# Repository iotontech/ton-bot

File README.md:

TON-BOT V1.1
========

O robô **TON-BOT** é um kit de robótica móvel 3 em 1 com a **Plataforma TON**, destinado ao aprendizado no desenvolvimento de robôs solucionadores de labirinto (micromouse) e robôs seguidores de linha (robotracer). Também podendo ser controlado sem fio pelo Bluetooth.

# Características do Kit

* Motores: micromotor Pololu com caixa de redução de metal - 1000 rpm
* Rodas: 32x7mm (plástico e borracha)
* Encoders: magnético em quadratura - 360 ppr
* 8 Sensores de linha: QRE1113GR
* 4 Sensores de parede: SFH4545 (LED) / TEFT4300 (fototransistor)
* Ponte H dos motores: TB6612FNG
* Bateria: LiPo 1S 600mAh

Com os recursos do **TON** o kit possui: Carregador integrado + Monitor de bateria + Bluetooth 4.0 + Buzzer + accel/gyro/mag + LED RGB + Wi-Fi

# Primeiros Passos

1. Execute o código de testes do robô:
    * O **TON-BOT** é enviado com o código [ton-bot_teste](https://github.com/iotontech/ton-bot_teste) já gravado!
    * Então, conecte o robô em uma porta USB e abra o terminal (baudrate 115200)
    * São apresentadas as leituras de todos os sensores
    * Para testar os motores basta ligar a chave *MOTORS* e pressionar o botão *USER*
    * **Para recarregar a bateria:** conecte o robô no carregador com o botão *USER* pressionado (pode liberá-lo logo em seguida). Quando o LED estiver verde e piscando indica que a bateria já está carregada
2. Siga os passos deste [link](https://github.com/iotontech/IOTON-IDE) para a instalação da *IOTON-IDE* **OU** siga este [tutorial](https://github.com/iotontech/ioton-mbed-online) para usar o *mbed Online Compiler*
3. Programando seu robô:
    * Faça uma cópia do [código de teste](https://github.com/iotontech/ton-bot_teste) e utilize ele de referência
    * Abra o **Editor Atom** e adicione a pasta do projeto: `File→Add Project Folder...`
    * Edite o arquivo *main.cpp*
4. Procedimentos para gravação do código no robô:
    * Colocar o TON no modo **BOOT**: pressionar o botão *RESET/BOOT* por mais de 1s
    * Realizar o **upload**: clicar no botão *“PlatformIO: Upload”* (icone: seta para direita)
    * Aguardar o término do processo
    * Voltar o TON para a execução: pressione rapidamente o botão *RESET/BOOT*

# License

Copyright IOTON Technology 2017.

This documentation describes Open Hardware and is licensed under the CERN OHL v. 1.2.
You may redistribute and modify this documentation under the terms of the CERN OHL v.1.2. (http://ohwr.org/cernohl). This documentation is distributed WITHOUT ANY EXPRESS OR IMPLIED WARRANTY, INCLUDING OF MERCHANTABILITY, SATISFACTORY QUALITY AND FITNESS FOR A PARTICULAR PURPOSE. Please see the CERN OHL v.1.2 for applicable conditions.

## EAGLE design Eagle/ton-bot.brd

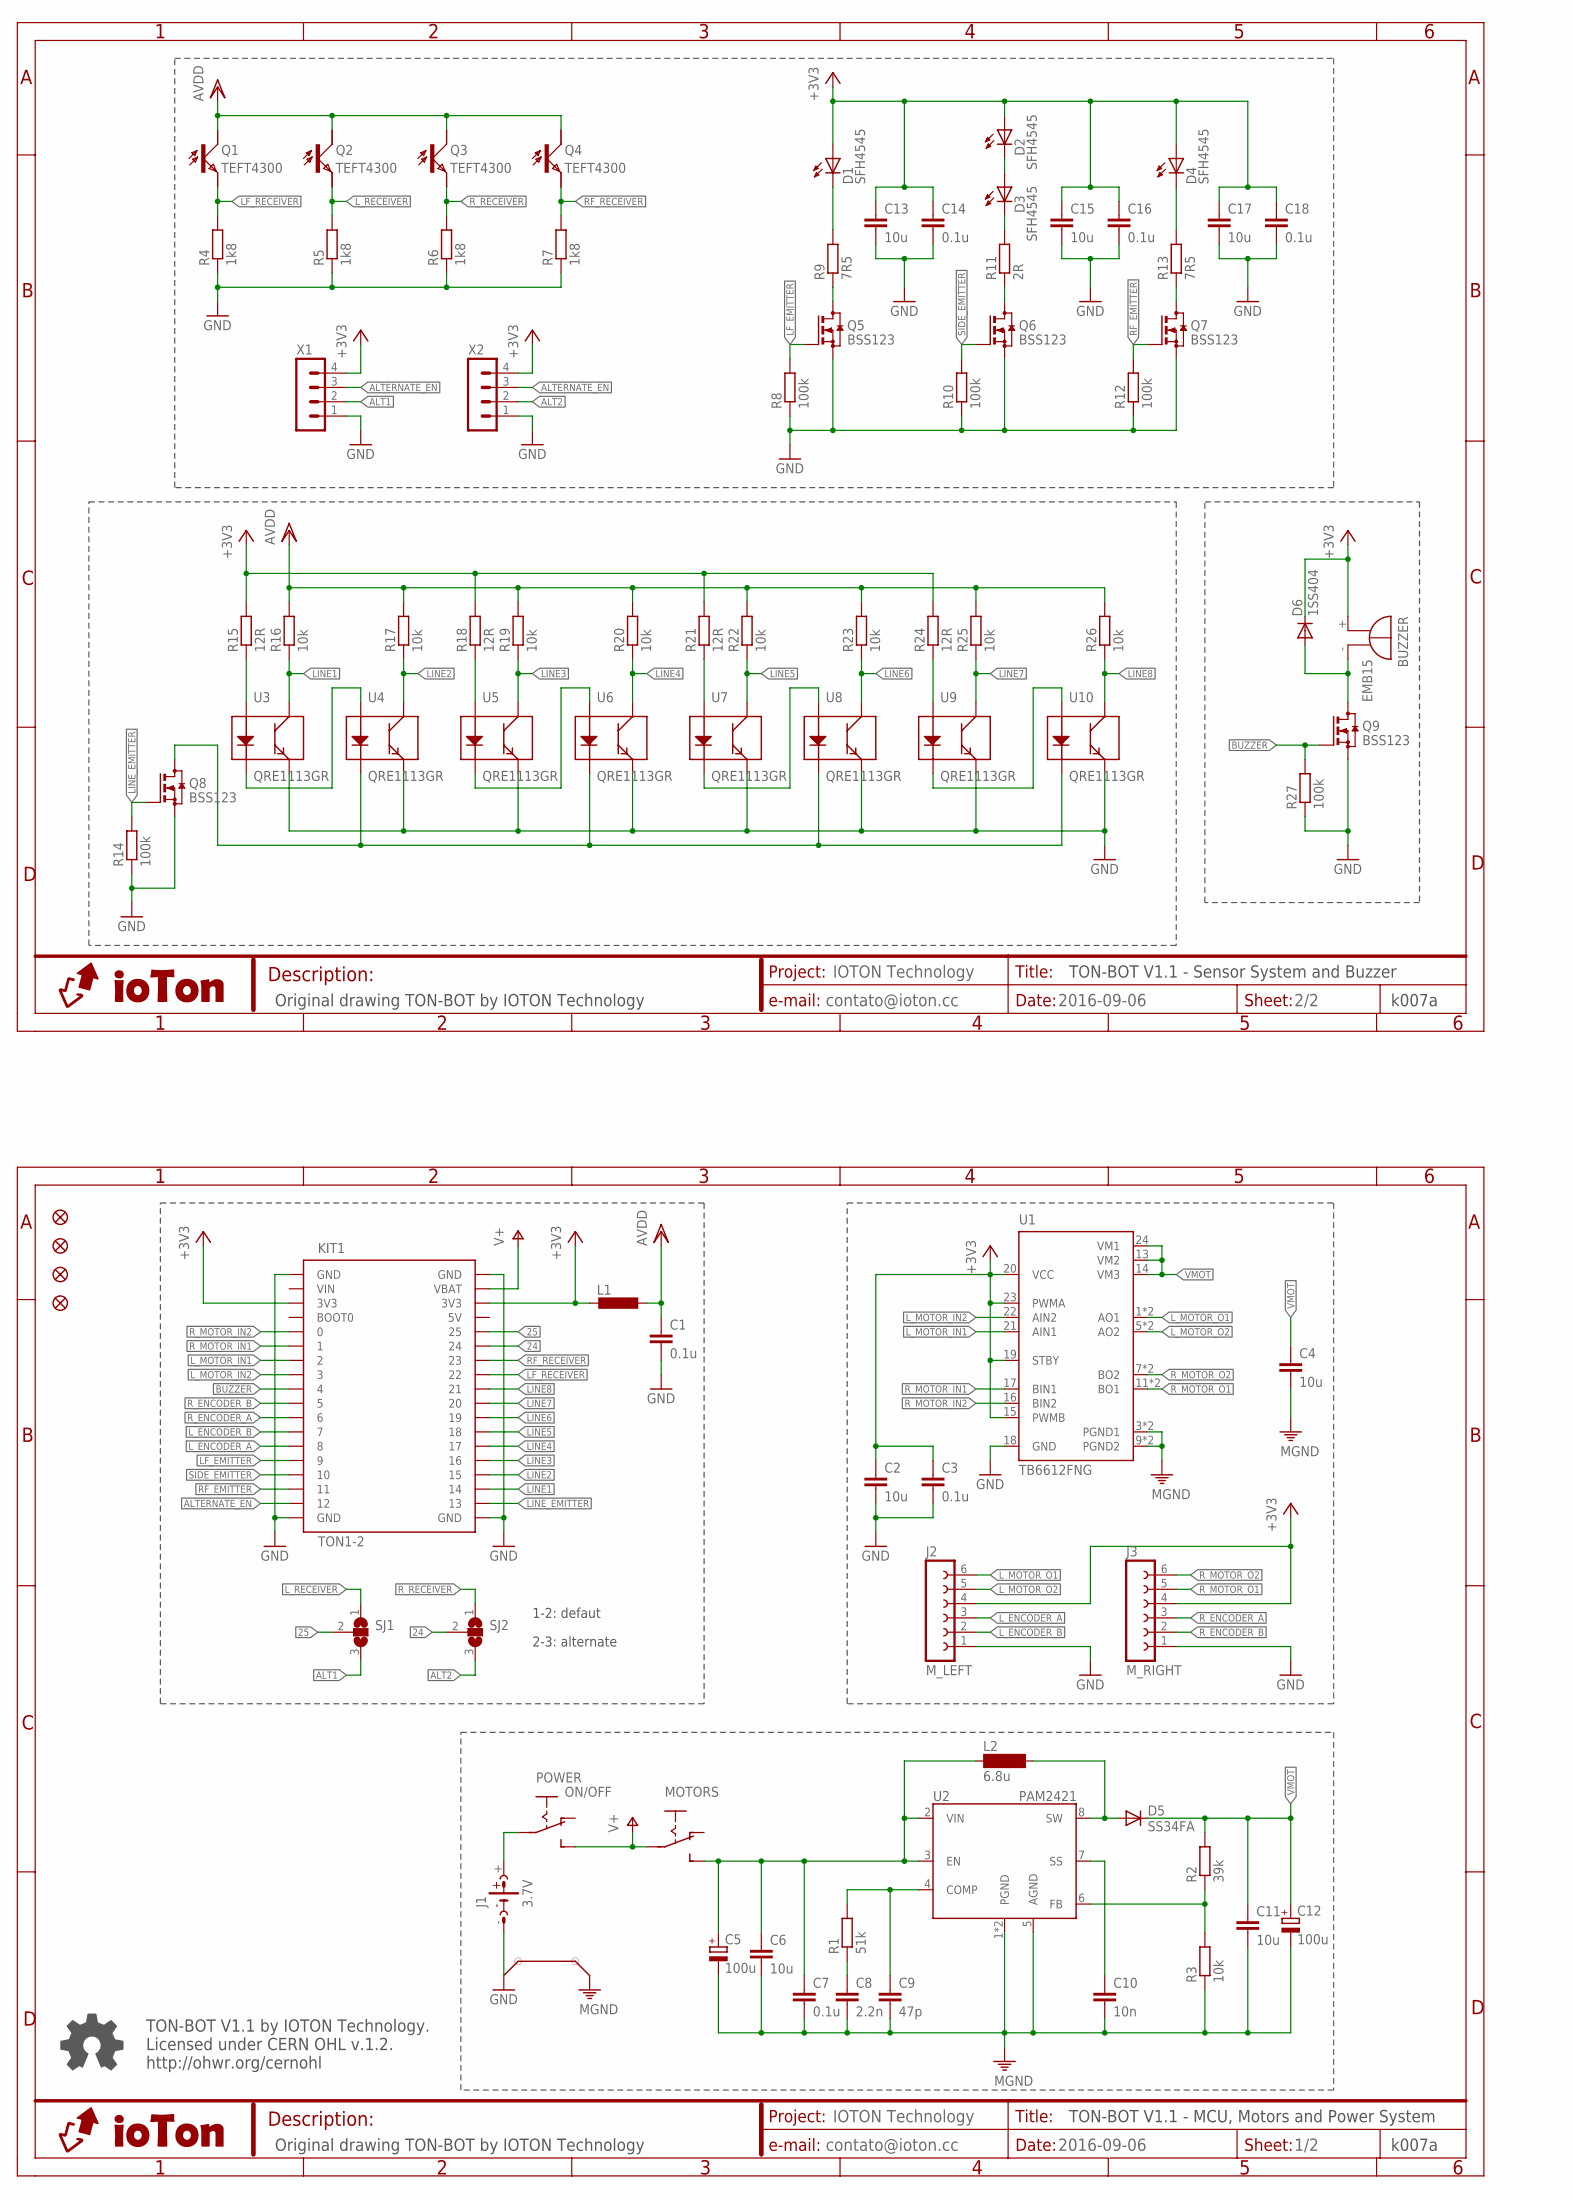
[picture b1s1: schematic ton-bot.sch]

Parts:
BUZZER: EMB15; BMT1205XH7.5
C1, C3, C7, C14, C16, C18: 0.1u; C0603
C2, C4, C6, C11, C13, C15, C17: 10u; C0805
C5, C12: 100u; 153CLV-0505
C8: 2.2n; C0603
C9: 47p; C0603
C10: 10n; C0603
D1: SFH4545; SFH4545-AK
D2, D3, D4: SFH4545; SFH4545-KA
D5: SS34FA; DO214BA
D6: 1SS404; SOD323-R
J1: 3.7V; BATTERY
J2: M_LEFT; CON6-1_2MM
J3: M_RIGHT; CON6-1_2MM
JP1, JP2, JP3, JP4: FIDUCIAL1X2; FIDUCIAL-1X2
KIT1: TON1-2
L1: L-EUL0603; L0603
L2: 6.8u; TYS6045
MOTORS: SWITCHS; SWITCH
POWER: ON/OFF; SWITCH
Q1, Q3: TEFT4300; TEFT4300-CE
Q2, Q4: TEFT4300; TEFT4300-EC
Q5, Q6, Q7, Q8, Q9: BSS123; SOT23
R1: 51k; R0603
R2: 39k; R0603
R3, R16, R17, R19, R20, R22, R23, R25, R26: 10k; R0603
R4, R5, R6, R7: 1k8; R0603
R8, R10, R12, R14, R27: 100k; R0603
R9, R13: 7R5; R0805
R11: 2R; R0805
R15, R18, R21, R24: 12R; R0603
SJ1, SJ2: SJ2W; SJ_2
U1: TB6612FNG; SSOP24
U2: PAM2421; SO-08EP
U3, U4, U5, U6, U7, U8, U9, U10: QRE1113GR; QRE1113
X1, X2: MA04-1; PIN4-1

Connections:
5V: KIT1.EXT-2.4 (5V)
24: KIT1.EXT-2.6 (24), SJ2.2
25: KIT1.EXT-2.5 (25), SJ1.2
+3V3: BUZZER.+, C2.1, C3.1, C13.1, C14.1, C15.1, C16.1, C17.1, C18.1, D1.A, D2.A, D4.A, D6.C, J2.4, J3.4, KIT1.EXT-1.3 (3V3), KIT1.EXT-2.3 (3V3), L1.2, R15.2, R18.2, R21.2, R24.2, U1.15 (PWMB), U1.19 (STBY), U1.20 (VCC), U1.23 (PWMA), X1.4, X2.4
ALT1: SJ1.3, X1.2
ALT2: SJ2.3, X2.2
ALTERNATE_EN: KIT1.EXT-1.17 (12), X1.3, X2.3
A_VDD: C1.1, L1.1, Q1.C, Q2.C, Q3.C, Q4.C, R16.2, R17.2, R19.2, R20.2, R22.2, R23.2, R25.2, R26.2
BUZZER: KIT1.EXT-1.9 (4), Q9.1 (G), R27.2
FDSG: D5.A, L2.2, U2.8 (SW)
GND: C1.2, C2.2, C3.2, C13.2, C14.2, C15.2, C16.2, C17.2, C18.2, J1.-, J2.1, J3.1, KIT1.EXT-1.1 (GND), KIT1.EXT-1.18 (GND), KIT1.EXT-2.1 (GND), KIT1.EXT-2.18 (GND), KIT1.GND1 (GND), KIT1.GND2 (GND), Q5.2 (S), Q6.2 (S), Q7.2 (S), Q8.2 (S), Q9.2 (S), R4.1, R5.1, R6.1, R7.1, R8.1, R10.1, R12.1, R14.1, R27.1, U1.18 (GND), U3.4 (E), U4.4 (E), U5.4 (E), U6.4 (E), U7.4 (E), U8.4 (E), U9.4 (E), U10.4 (E), X1.1, X2.1
LF_EMITTER: KIT1.EXT-1.14 (9), Q5.1 (G), R8.2
LF_RECEIVER: KIT1.EXT-2.8 (22), Q1.E, R4.2
LINE1: KIT1.EXT-2.16 (14), R16.1, U3.3 (C)
LINE2: KIT1.EXT-2.15 (15), R17.1, U4.3 (C)
LINE3: KIT1.EXT-2.14 (16), R19.1, U5.3 (C)
LINE4: KIT1.EXT-2.13 (17), R20.1, U6.3 (C)
LINE5: KIT1.EXT-2.12 (18), R22.1, U7.3 (C)
LINE6: KIT1.EXT-2.11 (19), R23.1, U8.3 (C)
LINE7: KIT1.EXT-2.10 (20), R25.1, U9.3 (C)
LINE8: KIT1.EXT-2.9 (21), R26.1, U10.3 (C)
LINE_EMITTER: KIT1.EXT-2.17 (13), Q8.1 (G), R14.2
LINE_K: Q8.3 (D), U4.2 (K), U6.2 (K), U8.2 (K), U10.2 (K)
L_ENCODER_A: J2.3, KIT1.EXT-1.13 (8)
L_ENCODER_B: J2.2, KIT1.EXT-1.12 (7)
L_MOTOR_IN1: KIT1.EXT-1.7 (2), U1.21 (AIN1)
L_MOTOR_IN2: KIT1.EXT-1.8 (3), U1.22 (AIN2)
L_MOTOR_O1: J2.6, U1.1 (AO1), U1.2 (AO1)
L_MOTOR_O2: J2.5, U1.5 (AO2), U1.6 (AO2)
L_RECEIVER: Q2.E, R5.2, SJ1.1
M_GND: C4.2, C5.-, C6.2, C7.2, C8.2, C9.2, C10.2, C11.2, C12.-, R3.1, U1.3 (PGND1), U1.4 (PGND1), U1.9 (PGND2), U1.10 (PGND2), U2.1 (PGND), U2.5 (AGND), U2.EXP (PGND)
unnamed: Q5.3 (D), R9.1
unnamed: Q6.3 (D), R11.1
unnamed: Q7.3 (D), R13.1
unnamed: BUZZER.-, D6.A, Q9.3 (D)
unnamed: R2.1, R3.2, U2.6 (FB)
unnamed: C10.1, U2.7 (SS)
unnamed: C8.1, R1.1
unnamed: C9.1, R1.2, U2.4 (COMP)
unnamed: D2.K, D3.A
unnamed: D1.K, R9.2
unnamed: D4.K, R13.2
unnamed: J1.+, POWER.P
unnamed: D3.K, R11.2
unnamed: R15.1, U3.1 (A)
unnamed: U3.2 (K), U4.1 (A)
unnamed: U5.2 (K), U6.1 (A)
unnamed: U7.2 (K), U8.1 (A)
unnamed: U9.2 (K), U10.1 (A)
unnamed: R24.1, U9.1 (A)
unnamed: R21.1, U7.1 (A)
unnamed: R18.1, U5.1 (A)
RF_EMITTER: KIT1.EXT-1.16 (11), Q7.1 (G), R12.2
RF_RECEIVER: KIT1.EXT-2.7 (23), Q4.E, R7.2
R_ENCODER_A: J3.3, KIT1.EXT-1.11 (6)
R_ENCODER_B: J3.2, KIT1.EXT-1.10 (5)
R_MOTOR_IN1: KIT1.EXT-1.6 (1), U1.17 (BIN1)
R_MOTOR_IN2: KIT1.EXT-1.5 (0), U1.16 (BIN2)
R_MOTOR_O1: J3.5, U1.11 (BO1), U1.12 (BO1)
R_MOTOR_O2: J3.6, U1.7 (BO2), U1.8 (BO2)
R_RECEIVER: Q3.E, R6.2, SJ2.1
SIDE_EMITTER: KIT1.EXT-1.15 (10), Q6.1 (G), R10.2
V+: KIT1.EXT-2.2 (VBAT), MOTORS.P, POWER.S
VIN: KIT1.EXT-1.2 (VIN)
VIN_M: C5.+, C6.1, C7.1, L2.1, MOTORS.S, U2.2 (VIN), U2.3 (EN)
VMOT: C4.1, C11.1, C12.+, D5.C, R2.2, U1.13 (VM2), U1.14 (VM3), U1.24 (VM1)

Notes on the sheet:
1-2: defaut
2-3: alternate
TON-BOT V1.1 - MCU, Motors and Power System
TON-BOT V1.1 by IOTON Technology. Licensed under CERN OHL v.1.2. http://ohwr.org/cernohl
Original drawing TON-BOT by IOTON Technology
k007a
TON-BOT V1.1 - Sensor System and Buzzer

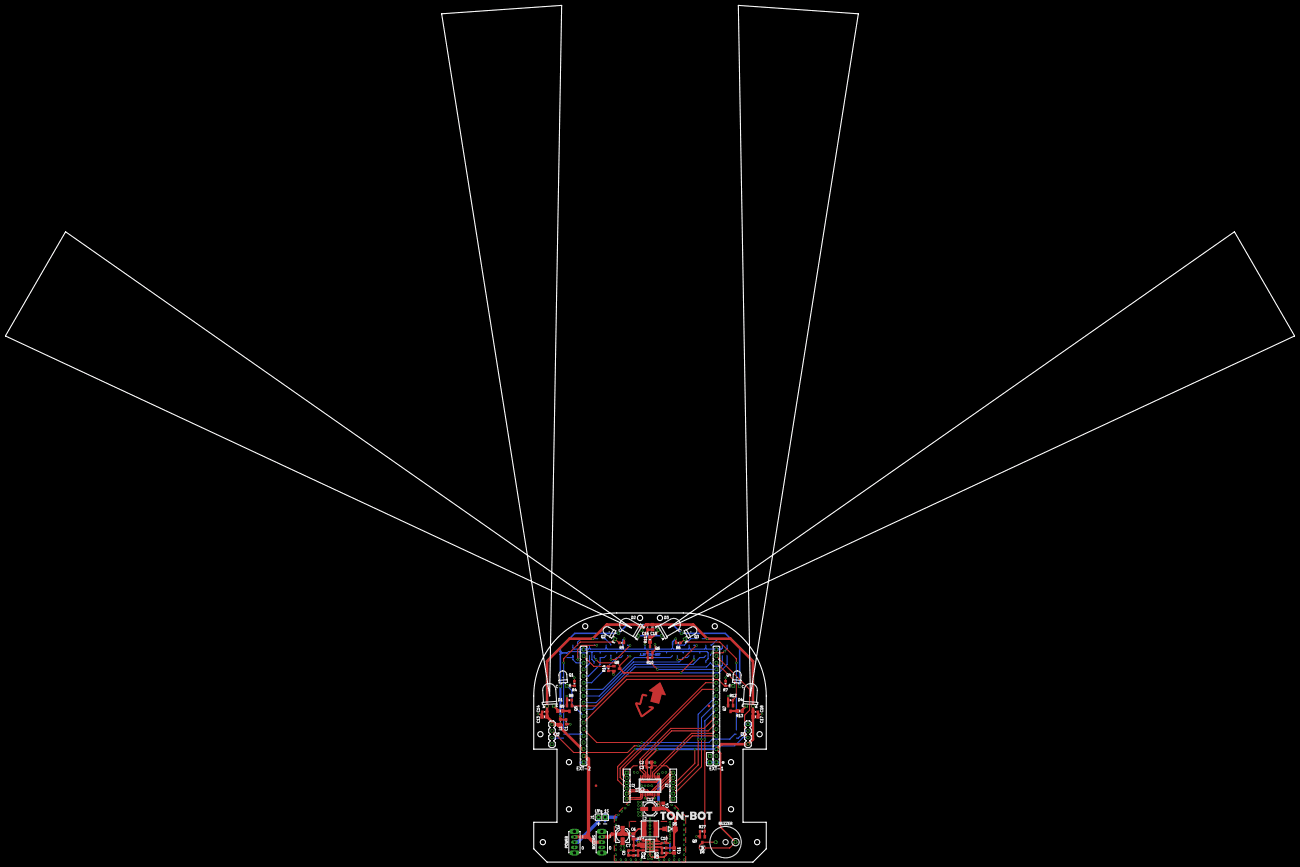
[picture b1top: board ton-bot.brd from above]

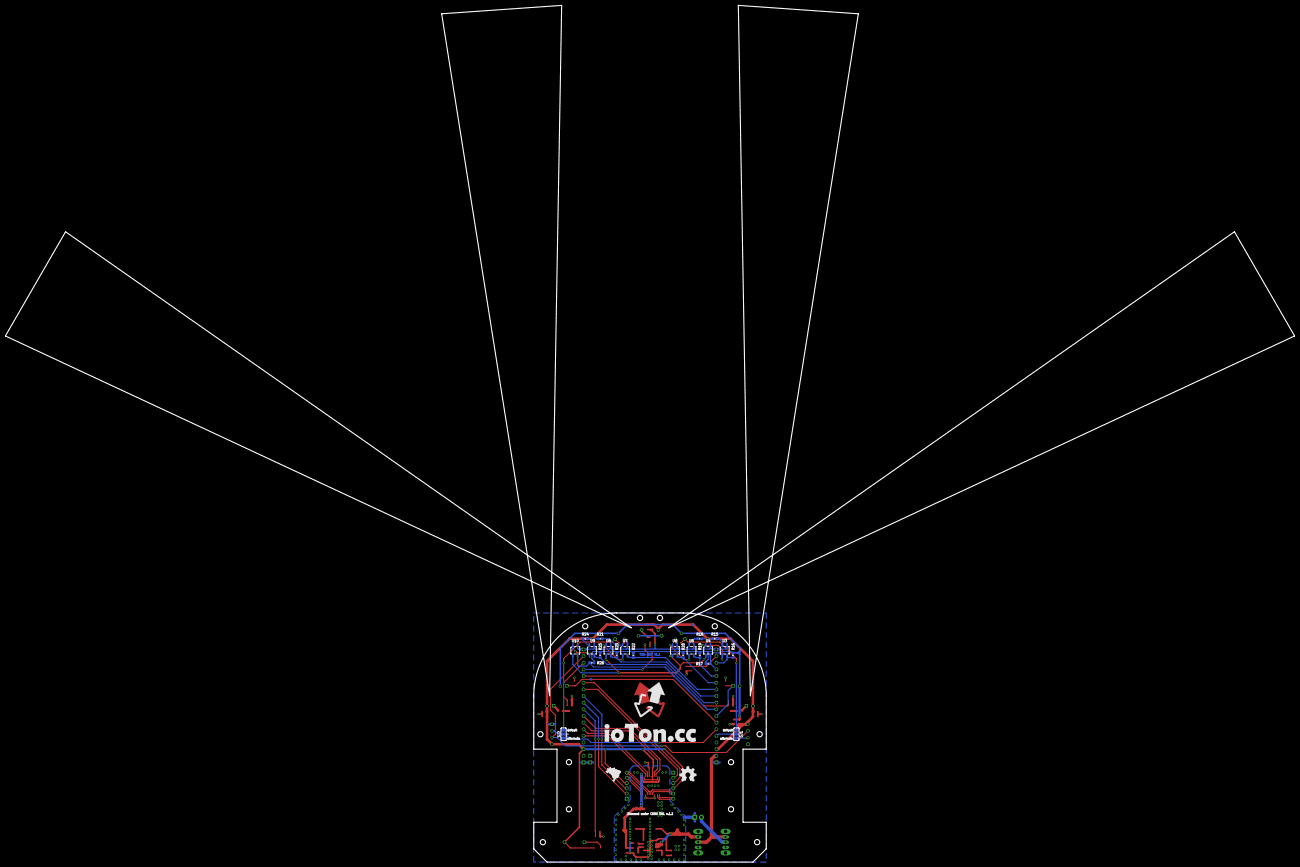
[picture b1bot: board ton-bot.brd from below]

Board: 2 copper layers, 492.9 x 327.5 mm, 87 parts (24 on the bottom side), 64 nets.

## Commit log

2017-06-24 First commit - Release v1.1.0

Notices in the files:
parts and their libraries:
SparkFun: Licensing: CC v3.0 Share-Alike You are welcome to use this library for commercial purposes.
